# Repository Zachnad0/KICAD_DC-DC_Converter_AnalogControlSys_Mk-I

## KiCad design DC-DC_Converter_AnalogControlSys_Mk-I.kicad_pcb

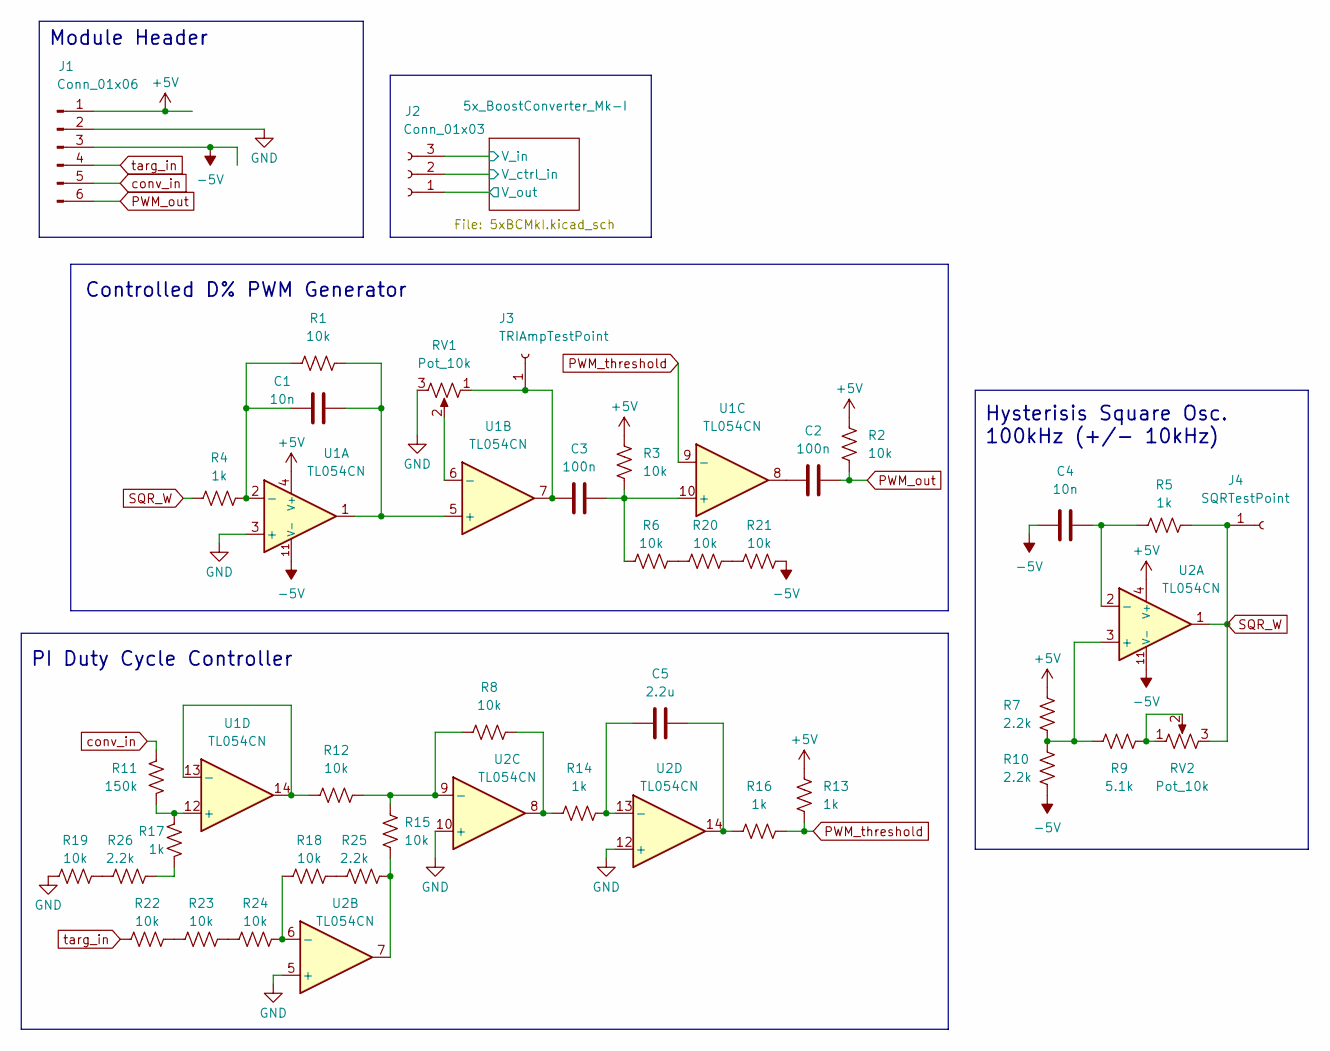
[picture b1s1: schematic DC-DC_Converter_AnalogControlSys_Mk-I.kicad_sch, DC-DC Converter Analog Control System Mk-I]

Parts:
C1, C4: 10n; C_0805_2012Metric_Pad1.15x1.40mm; LCSC Part # C52278
C2, C3: 100n; C_0805_2012Metric_Pad1.15x1.40mm; LCSC Part # C520083
C5: 2.2u; C_0603_1608Metric_Pad1.05x0.95mm; LCSC Part # C415535
J1: Conn_01x06; PinHeader_1x06_P2.54mm_Vertical; LCSC Part # N/A
J2: Conn_01x03; PinHeader_1x03_P2.54mm_Vertical; LCSC Part # N/A
J3: TRIAmpTestPoint; PinHeader_1x01_P2.54mm_Vertical; LCSC Part # N/A
J4: SQRTestPoint; PinHeader_1x01_P2.54mm_Vertical; LCSC Part # N/A
R1, R2, R3, R6, R8, R12, R15, R18, R19, R20, R21, R22, R23, R24: 10k; R_0805_2012Metric_Pad1.15x1.40mm; LCSC Part # C212284
R4, R5, R13, R14, R16, R17: 1k; R_0603_1608Metric_Pad0.98x0.95mm; LCSC Part # C209012
R7, R10, R25, R26: 2.2k; R_0603_1608Metric_Pad0.98x0.95mm; LCSC Part # C423061
R9: 5.1k; R_0603_1608Metric_Pad0.98x0.95mm; LCSC Part # C318133
R11: 150k; R_0805_2012Metric_Pad1.15x1.40mm; LCSC Part # C966565
RV1, RV2: Pot_10k; JIERR 3362P Pot; LCSC Part # C48997914
U1, U2: TL054CN; DIP-14_W7.62mm; LCSC Part # C1347256

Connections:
+5V: J1.1, R2.2, R3.2, R7.2, R13.1, U1.4 (V+), U2.4 (V+)
-5V: C4.1, J1.3, R10.1, R21.1, U1.11 (V-), U2.11 (V-)
/5x_BoostConverter_Mk-I/V_ctrl_in: J2.2; also elsewhere on the board
/5x_BoostConverter_Mk-I/V_in: J2.3; also elsewhere on the board
/5x_BoostConverter_Mk-I/V_out: J2.1; also elsewhere on the board
GND: J1.2, R19.2, RV1.3, U1.3 (+), U2.5 (+), U2.10 (+), U2.12 (+); also elsewhere on the board
unnamed: C2.1, U1.8
unnamed: C5.2, R16.2, U2.14
unnamed: C3.1, J3.1, RV1.1, U1.7
unnamed: R9.2, RV2.1, RV2.2
unnamed: R8.1, R14.2, U2.8
unnamed: R15.1, R25.2, U2.7
unnamed: R17.1, R26.2
unnamed: R18.1, R25.1
unnamed: R19.1, R26.1
unnamed: R20.1, R21.2
unnamed: R6.1, R20.2
unnamed: R22.1, R23.2
unnamed: R23.1, R24.2
unnamed: C1.1, R1.1, R4.2, U1.2 (-)
unnamed: C1.2, R1.2, U1.1, U1.5 (+)
unnamed: RV1.2, U1.6 (-)
unnamed: C3.2, R3.1, R6.2, U1.10 (+)
unnamed: R11.2, R17.2, U1.12 (+)
unnamed: R12.2, U1.13 (-), U1.14
unnamed: R7.1, R9.1, R10.2, U2.3 (+)
unnamed: C4.2, R5.1, U2.2 (-)
unnamed: R18.2, R24.1, U2.6 (-)
unnamed: R8.2, R12.1, R15.2, U2.9 (-)
unnamed: C5.1, R14.1, U2.13 (-)
PWM_out: C2.2, J1.6, R2.1
PWM_threshold: R13.2, R16.1, U1.9 (-)
SQR_W: J4.1, R4.1, R5.2, RV2.3, U2.1
conv_in: J1.5, R11.1
targ_in: J1.4, R22.2

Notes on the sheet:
Hysterisis Square Osc. 100kHz (+/- 10kHz)
Module Header
Controlled D% PWM Generator
PI Duty Cycle Controller

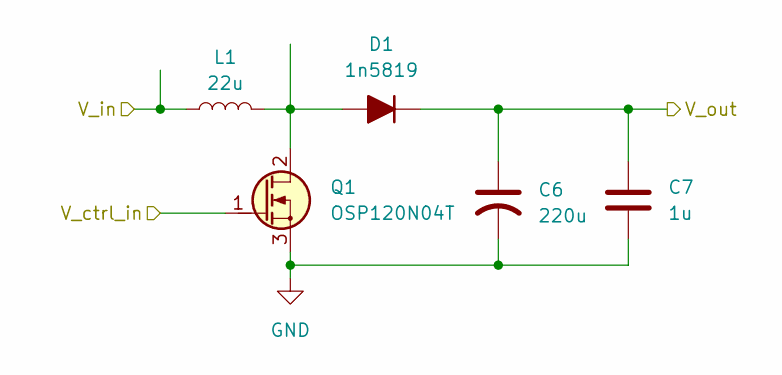
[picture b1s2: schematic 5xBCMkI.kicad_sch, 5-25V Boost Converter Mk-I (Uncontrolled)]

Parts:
C6: 220u; CP_Radial_D10.0mm_P5.00mm; LCSC Part # C7499951
C7: 1u; C_Axial_L3.0mm_D2.3mm_P7.50mm_Horizontal; LCSC Part # C94708
D1: 1n5819; D_DO-41_SOD81_P10.16mm_Horizontal; LCSC Part # C402218
L1: 22u; L_Radial_D12.0mm_P5.00mm_Fastron_11P; LCSC Part # C142471
Q1: OSP120N04T; TO-220-3_Vertical_GDS; LCSC Part # C51949596

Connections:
/5x_BoostConverter_Mk-I/V_ctrl_in: Q1.1 (G); also elsewhere on the board
/5x_BoostConverter_Mk-I/V_in: L1.1; also elsewhere on the board
/5x_BoostConverter_Mk-I/V_out: C6.1, C7.1, D1.1 (K); also elsewhere on the board
GND: C6.2, C7.2, Q1.3 (S); also elsewhere on the board
unnamed: D1.2 (A), L1.2, Q1.2 (D)

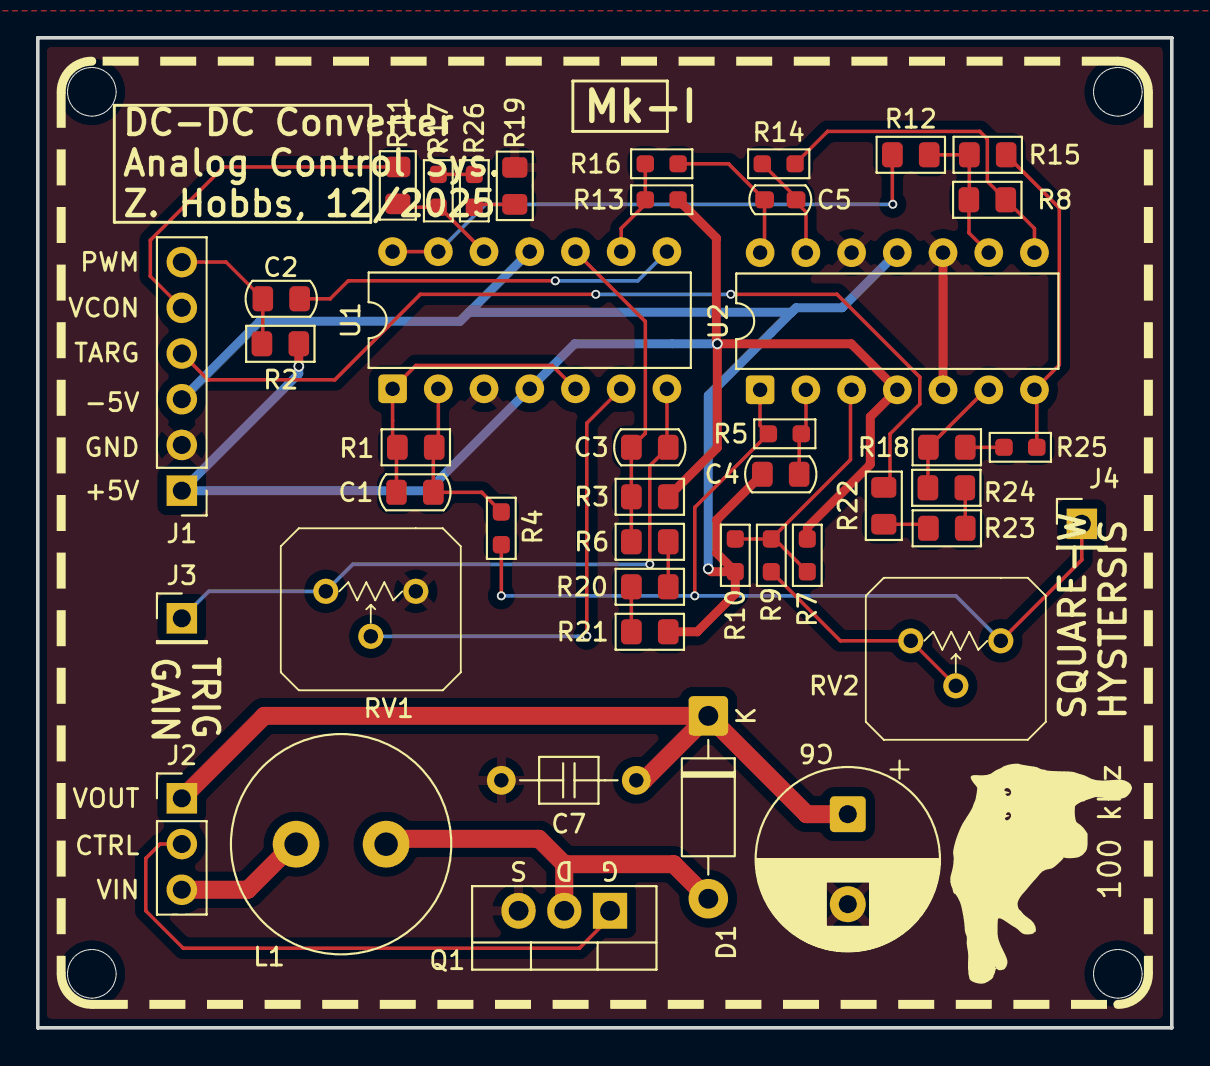
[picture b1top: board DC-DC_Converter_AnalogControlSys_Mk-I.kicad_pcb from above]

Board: 2 copper layers, 63.0 x 55.0 mm, 44 parts (0 on the bottom side), 36 nets.

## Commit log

2025-11-29 Project files initialized
2025-12-04 ADDED potentiometer footprint. ADDED layout of PI controller and PWM generator. TODO determine clock source, then assign component values and LCSC numbers.
2025-12-12 FIXED analog control system to work much better and matches the LTspice sim. ADDED optionally-usable 10W 5x boost converter module. TODO find and assign LCSC part numbers and footprints, before begin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
2025-12-13 ADDED LTspice simulation to repo. TODO update KiCAD schematic to match latest LTspice model.
2025-12-16 FIXED schematic to match simulation. TODO assign LCSC part numbers.
2025-12-17 ADDED all LCSC part numbers and footprints. FIXED schematic (and model) to use a smaller range of resistor and capacitor values to increase cost efficiency, at the expense of control system performan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
2025-12-17 WIP PCB layout
2025-12-17 DONE PCB layout and routing. TODO add some silkscreen text, double-check everything, then organize BOM and JLCPCB order.
2025-12-18 ADDED silkscreen graphics. DONE all checks on PCB validity. TODO double-check schematic, find suitable replacement for TL054, then order PCB and parts.
2025-12-19 Finalized design files for assembly and organized BOM.
